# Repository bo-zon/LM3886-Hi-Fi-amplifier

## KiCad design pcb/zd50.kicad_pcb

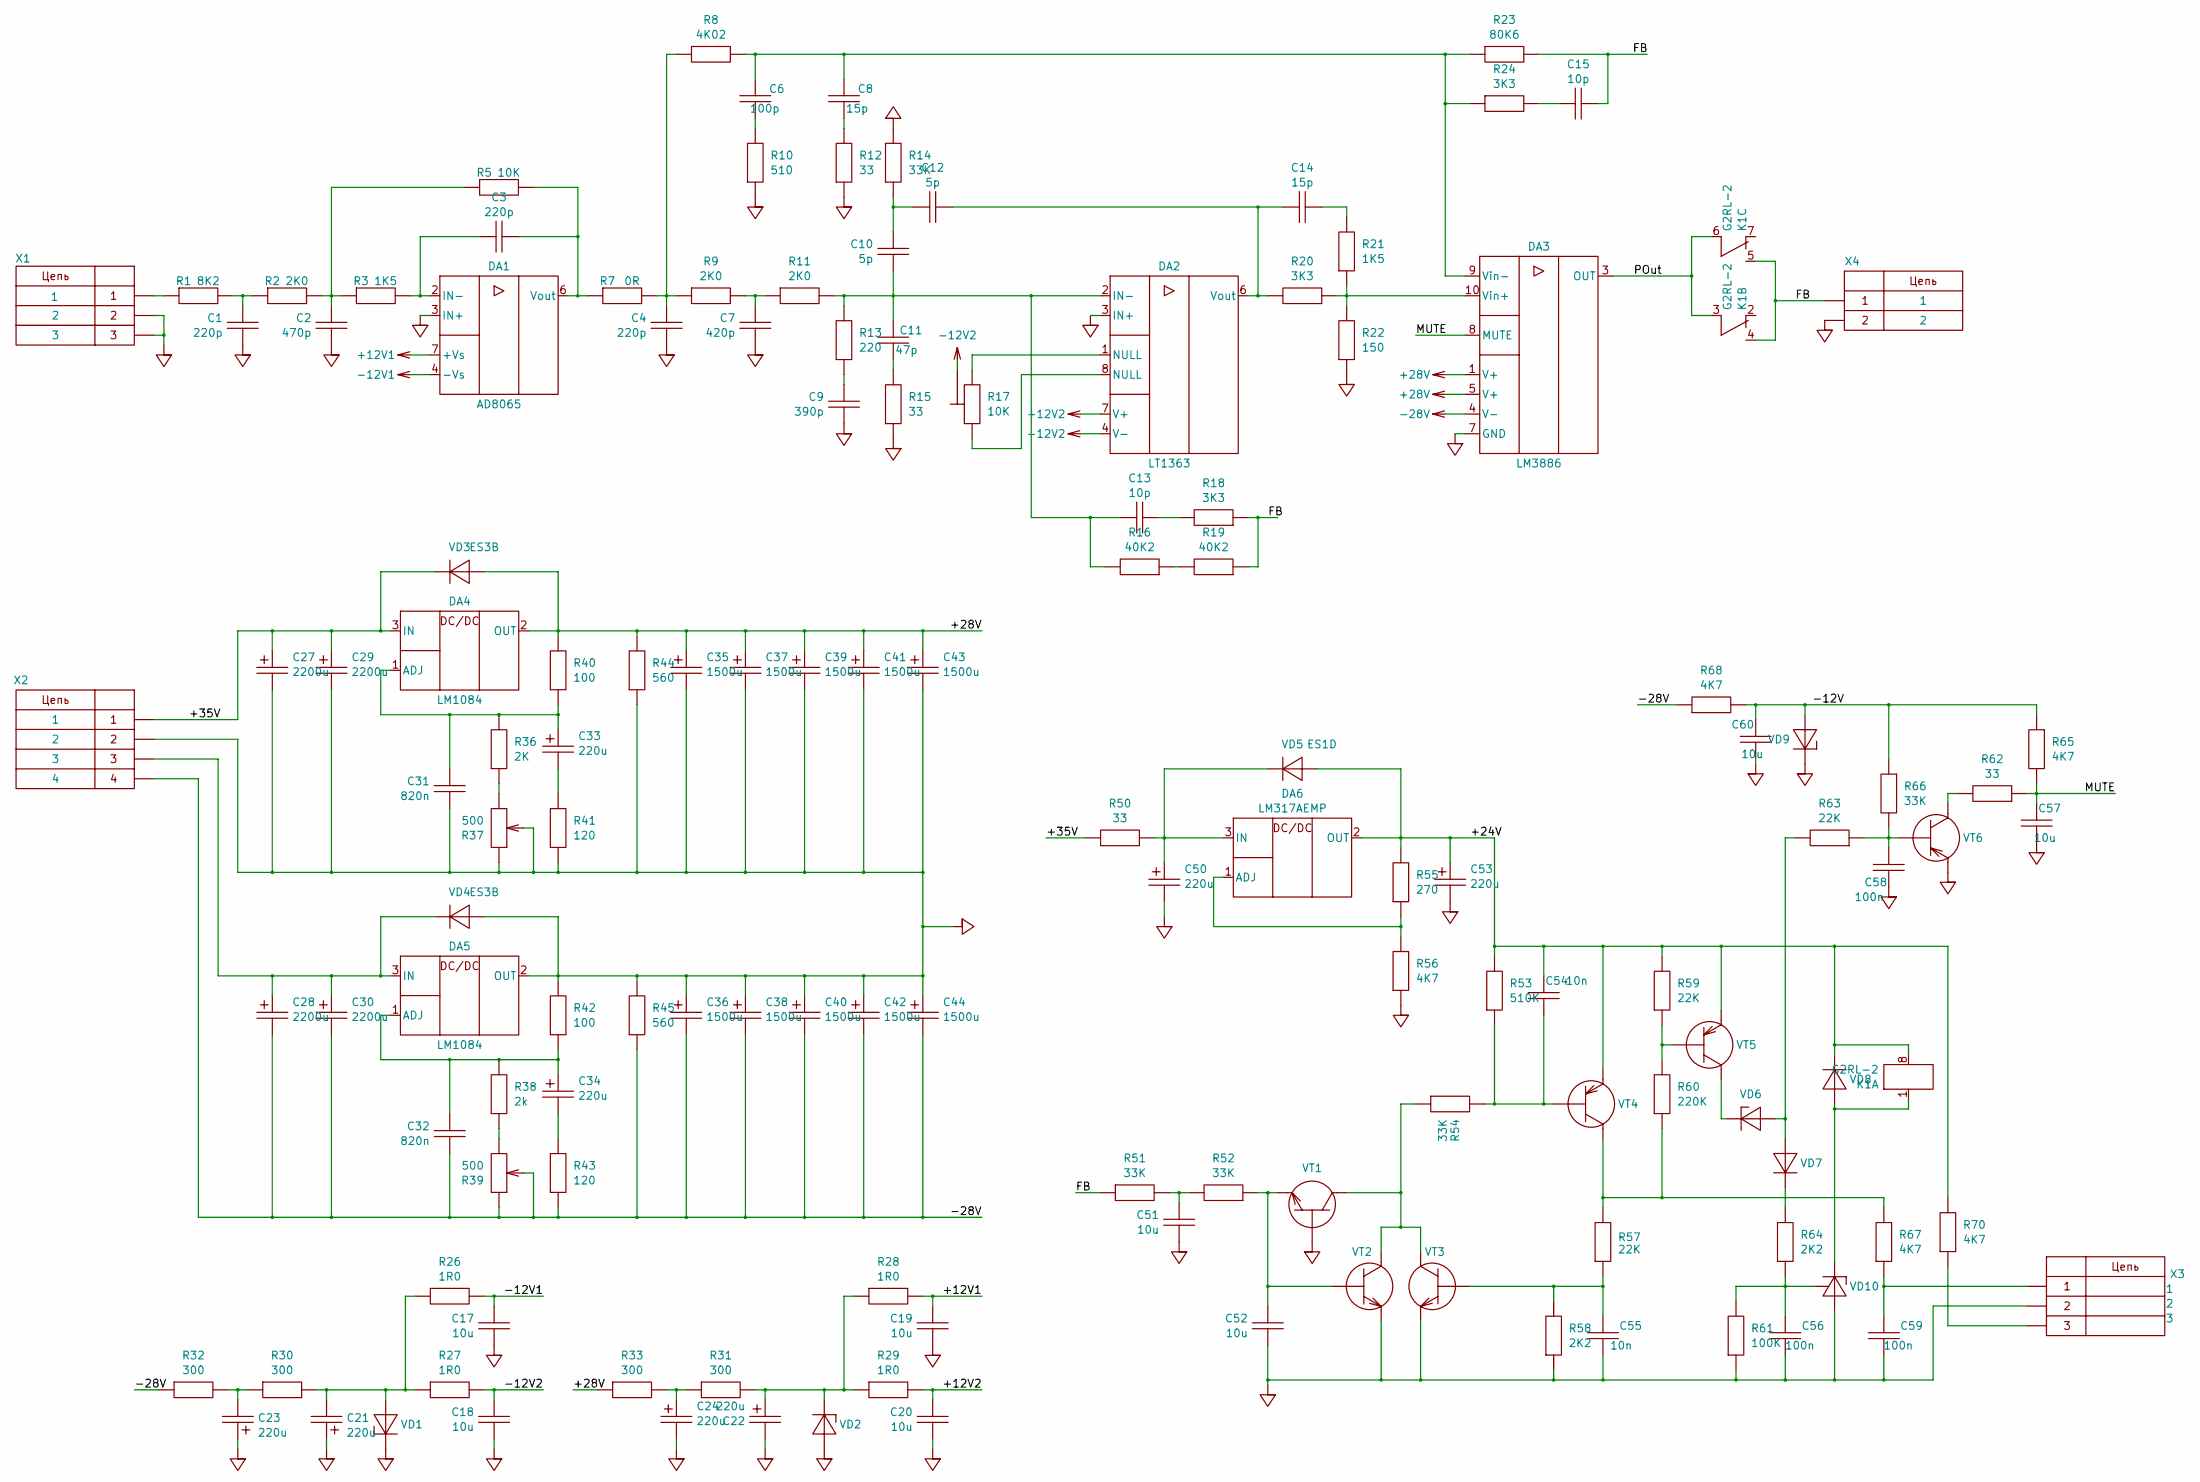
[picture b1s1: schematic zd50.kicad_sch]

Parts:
C1, C3, C4: 220p; C_0805_2012Metric
C2: 470p; C_0805_2012Metric
C6: 100p; C_0805_2012Metric
C7: 420p; C_0805_2012Metric
C8, C14: 15p; C_0805_2012Metric
C9: 390p; C_0805_2012Metric
C10, C12: 5p; C_0805_2012Metric
C11: 47p; C_0805_2012Metric
C13, C15: 10p; C_0805_2012Metric
C17, C18, C19, C20, C51, C52, C57, C60: 10u; C_1206_3216Metric
C21, C22, C23, C24: 220u; CP_Elec_8x10.5
C27, C28, C29, C30: 2200u; CP_Radial_D18.0mm_P7.50mm
C31, C32: 820n; C_Rect_L7.2mm_W7.2mm_P5.00mm_FKS2_FKP2_MKS2_MKP2
C33, C34, C50, C53: 220u; CP_Elec_10x10.5
C35, C36, C37, C38, C39, C40, C41, C42, C43, C44: 1500u; CP_Radial_D12.5mm_P5.00mm
C54, C55: 10n; C_0805_2012Metric
C56, C58, C59: 100n; C_0805_2012Metric
DA1: AD8065; SOIC-8_3.9x4.9mm_P1.27mm
DA2: LT1363; SOIC-8_3.9x4.9mm_P1.27mm
DA3: LM3886; TO-220-11_P3.4x2.54mm_StaggerOdd_Lead5.84mm_TabUp
DA4, DA5: LM1084; TO-220-3_Horizontal_TabUp
DA6: LM317AEMP; SOT-223-3_TabPin2
K1: G2RL-2; Relay_DPDT_Omron_G2RL-2
R1: 8K2; R_0805_2012Metric
R2, R9, R11: 2K0; R_0805_2012Metric
R3, R21: 1K5; R_0805_2012Metric
R5: 10K; R_0805_2012Metric
R7: 0R; R_0805_2012Metric
R8: 4K02; R_0805_2012Metric
R10: 510; R_0805_2012Metric
R12, R15, R50, R62: 33; R_0805_2012Metric
R13: 220; R_0805_2012Metric
R14, R51, R52, R54, R66: 33K; R_0805_2012Metric
R16, R19: 40K2; R_0805_2012Metric
R17: 10K; Potentiometer_Bourns_3314G_Vertical
R18, R20, R24: 3K3; R_0805_2012Metric
R22: 150; R_0805_2012Metric
R23: 80K6; R_0805_2012Metric
R26, R27, R28, R29: 1R0; R_0805_2012Metric
R30, R31, R32, R33: 300; R_1210_3225Metric
R36: 2K; R_2512_6332Metric
R37, R39: 500; Potentiometer_Bourns_3314G_Vertical
R38: 2k; R_2512_6332Metric
R40, R42: 100; R_0805_2012Metric
R41, R43: 120; R_0805_2012Metric
R44, R45: 560; R_Axial_DIN0414_L11.9mm_D4.5mm_P15.24mm_Horizontal
R53: 510K; R_0805_2012Metric
R55: 270; R_0805_2012Metric
R56, R65, R67, R68, R70: 4K7; R_0805_2012Metric
R57, R59, R63: 22K; R_0805_2012Metric
R58, R64: 2K2; R_0805_2012Metric
R60: 220K; R_0805_2012Metric
R61: 100K; R_0805_2012Metric
VD1, VD2, VD9: FLZ12V; D_MiniMELF
VD3, VD4: ES3B; D_SMB
VD5, VD8: ES1D; D_SMA
VD6: MMBTA56; D_MiniMELF
VD7: DL4148; D_MiniMELF
VD10: TL431; SOT-23-3
VT1, VT2, VT3: MMBTA06; SOT-23-3
VT4, VT5, VT6: MMBTA56; SOT-23-3
X1: CONN_3; SolderWire-0.5sqmm_1x03_P4.6mm_D0.9mm_OD2.1mm
X2: CONN_4; SolderWire-0.75sqmm_1x04_P7mm_D1.25mm_OD3.5mm
X3: CONN_3; SolderWire-0.25sqmm_1x03_P4.2mm_D0.65mm_OD1.7mm
X4: CONN_2; SolderWire-2sqmm_1x02_P7.8mm_D2mm_OD3.9mm

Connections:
+12V1: C19.1, DA1.7 (+Vs), R28.2
+12V2: C20.1, DA2.7 (V+), R29.2
+28V: C35.1, C37.1, C39.1, C41.1, C43.1, DA3.1 (V+), DA3.5 (V+), DA4.2 (OUT), R33.1, R40.2, R44.2, VD3.2 (A)
-12V1: C17.1, DA1.4 (-Vs), R26.2
-12V2: C18.1, DA2.4 (V-), R17.2, R27.2
-28V: C28.2, C30.2, C32.2, C36.2, C38.2, C40.2, C42.2, C44.2, DA3.4 (V-), R32.1, R39.1, R39.2, R43.1, R45.1, R68.1, X2.4
/+24V: C53.1, C54.1, DA6.2 (OUT), K1.8, R53.2, R55.2, R59.2, R70.2, VD5.2 (A), VD8.1 (K), VT4.2 (E), VT5.2 (E)
/+35V: C27.1, C29.1, DA4.3 (IN), R50.2, VD3.1 (K), X2.1
/-12V: C60.1, R65.1, R66.1, R68.2, VD9.2 (A)
/FB: C15.2, K1.4, K1.5, R18.1, R19.1, R23.2, R51.1, X4.1
/MUTE: C57.1, DA3.8 (MUTE), R62.1, R65.2
/POut: DA3.3 (OUT), K1.3, K1.6
GND: C1.2, C2.2, C4.2, C7.2, C9.2, C17.2, C18.2, C19.2, C20.2, C21.1, C22.2, C23.1, C24.2, C27.2, C29.2, C31.2, C35.2, C36.1, C37.2, C38.1, C39.2, C40.1, C41.2, C42.1, C43.2, C44.1, C50.2, C51.2, C52.2, C53.2, C55.2, C56.2, C57.2, C58.1, C59.2, C60.2, DA1.3 (IN+), DA2.3 (IN+), DA3.7 (GND), DA5.2 (OUT), R10.1, R12.1, R14.2, R15.1, R22.1, R37.1, R37.2, R41.1, R42.2, R44.1, R45.2, R56.1, R58.1, R61.1, VD1.1 (K), VD2.2 (A), VD4.2 (A), VD9.1 (K), VD10.3 (A), VT1.1 (B), VT2.2 (E), VT3.2 (E), VT6.2 (E), X1.2, X1.3, X2.2, X3.2, X4.2
unnamed: C1.1, R1.2, R2.1
unnamed: C2.1, R2.2, R3.1, R5.1
unnamed: C4.1, R7.2, R8.1, R9.1
unnamed: C6.2, R10.2
unnamed: C7.1, R9.2, R11.1
unnamed: C8.2, R12.2
unnamed: C9.1, R13.1
unnamed: C10.1, C12.1, R14.1
unnamed: C11.2, R15.2
unnamed: C13.2, R18.2
unnamed: C14.2, R21.2
unnamed: C15.1, R24.2
unnamed: C23.2, R30.1, R32.2
unnamed: C24.1, R31.1, R33.2
unnamed: C33.2, R41.2
unnamed: C34.2, R43.2
unnamed: C51.1, R51.2, R52.2
unnamed: C59.1, R67.1, X3.1
unnamed: C3.1, DA1.2 (IN-), R3.2
unnamed: C3.2, DA1.6 (Vout), R5.2, R7.1
unnamed: C10.2, C11.1, C13.1, DA2.2 (IN-), R11.2, R13.2, R16.2
unnamed: DA2.1 (NULL), R17.3
unnamed: DA2.8 (NULL), R17.1
unnamed: C12.2, C14.1, DA2.6 (Vout), R20.2
unnamed: DA3.10 (Vin+), R20.1, R21.1, R22.2
unnamed: C6.1, C8.1, DA3.9 (Vin-), R8.2, R23.1, R24.1
unnamed: C31.1, C33.1, DA4.1 (ADJ), R36.2, R40.1
unnamed: C32.1, C34.1, DA5.1 (ADJ), R38.2, R42.1
unnamed: C28.1, C30.1, DA5.3 (IN), VD4.1 (K), X2.3
unnamed: DA6.1 (ADJ), R55.1, R56.2
unnamed: C50.1, DA6.3 (IN), R50.1, VD5.1 (K)
unnamed: R1.1, X1.1
unnamed: R16.1, R19.2
unnamed: R36.1, R37.3
unnamed: R38.1, R39.3
unnamed: R70.1, X3.3
unnamed: C21.2, R26.1, R27.1, R30.2, VD1.2 (A)
unnamed: C22.1, R28.1, R29.1, R31.2, VD2.1 (K)
unnamed: R63.2, VD6.2 (A), VD7.2 (A)
unnamed: VD6.1 (K), VT5.3 (C)
unnamed: R64.2, VD7.1 (K)
unnamed: K1.1, VD8.2 (A), VD10.1 (K)
unnamed: C56.1, R61.2, R64.1, VD10.2 (REF)
unnamed: R54.1, VT1.3 (C), VT2.3 (C), VT3.3 (C)
unnamed: C52.1, R52.1, VT1.2 (E), VT2.1 (B)
unnamed: C55.1, R57.1, R58.2, VT3.1 (B)
unnamed: C54.2, R53.1, R54.2, VT4.1 (B)
unnamed: R57.2, R60.1, R67.2, VT4.3 (C)
unnamed: R59.1, R60.2, VT5.1 (B)
unnamed: C58.2, R63.1, R66.2, VT6.1 (B)
unnamed: R62.2, VT6.3 (C)

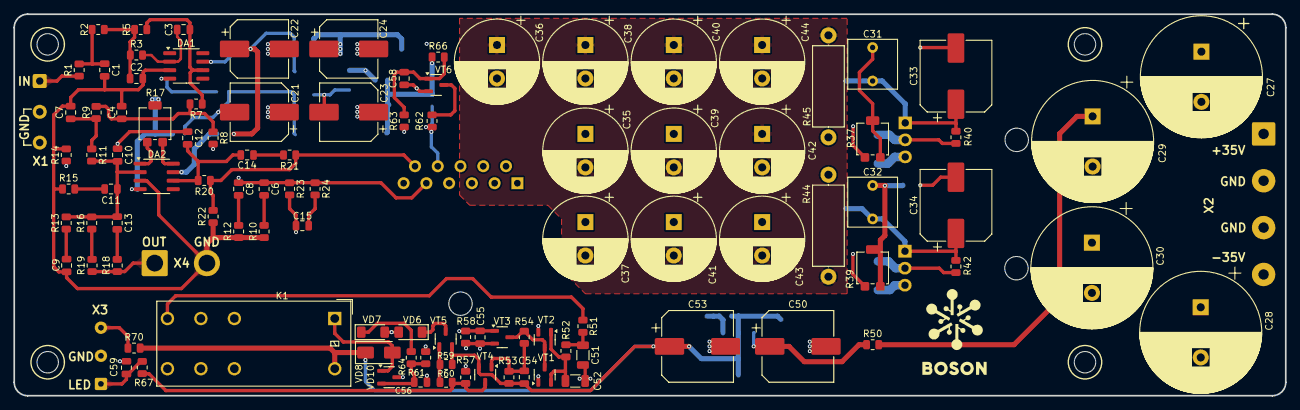
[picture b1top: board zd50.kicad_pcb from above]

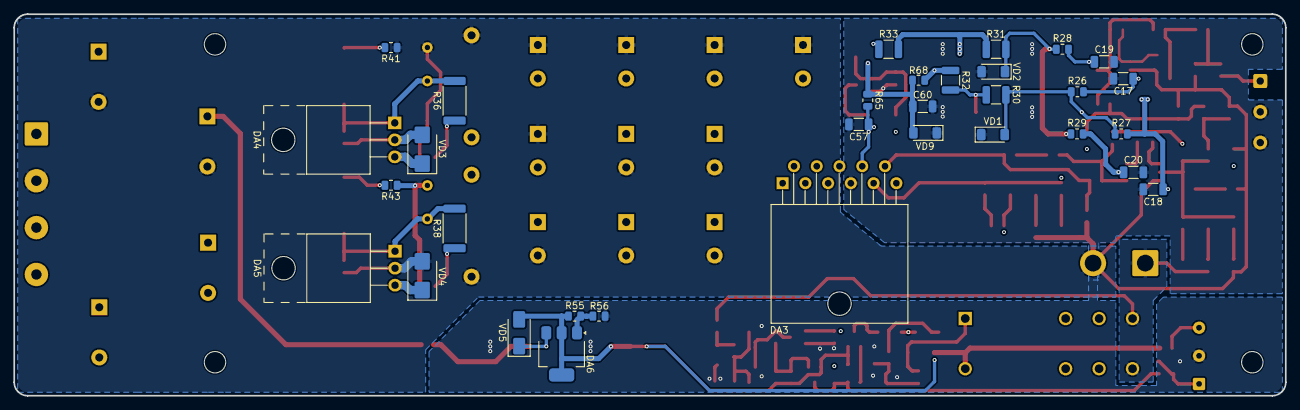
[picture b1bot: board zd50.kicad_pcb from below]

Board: 4 copper layers, 190.0 x 57.0 mm, 142 parts (32 on the bottom side), 64 nets.

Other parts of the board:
MH1, MH2, MH3, MH4: MountingHole_3.2mm_M3

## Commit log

2025-01-08 add original data
2025-01-15 add pcb and gerber
